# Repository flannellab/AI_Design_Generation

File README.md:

# AI_Design_Generation
Collection of things for AI generation of PCB designs (Components, Schematics, PCBs, Docs)

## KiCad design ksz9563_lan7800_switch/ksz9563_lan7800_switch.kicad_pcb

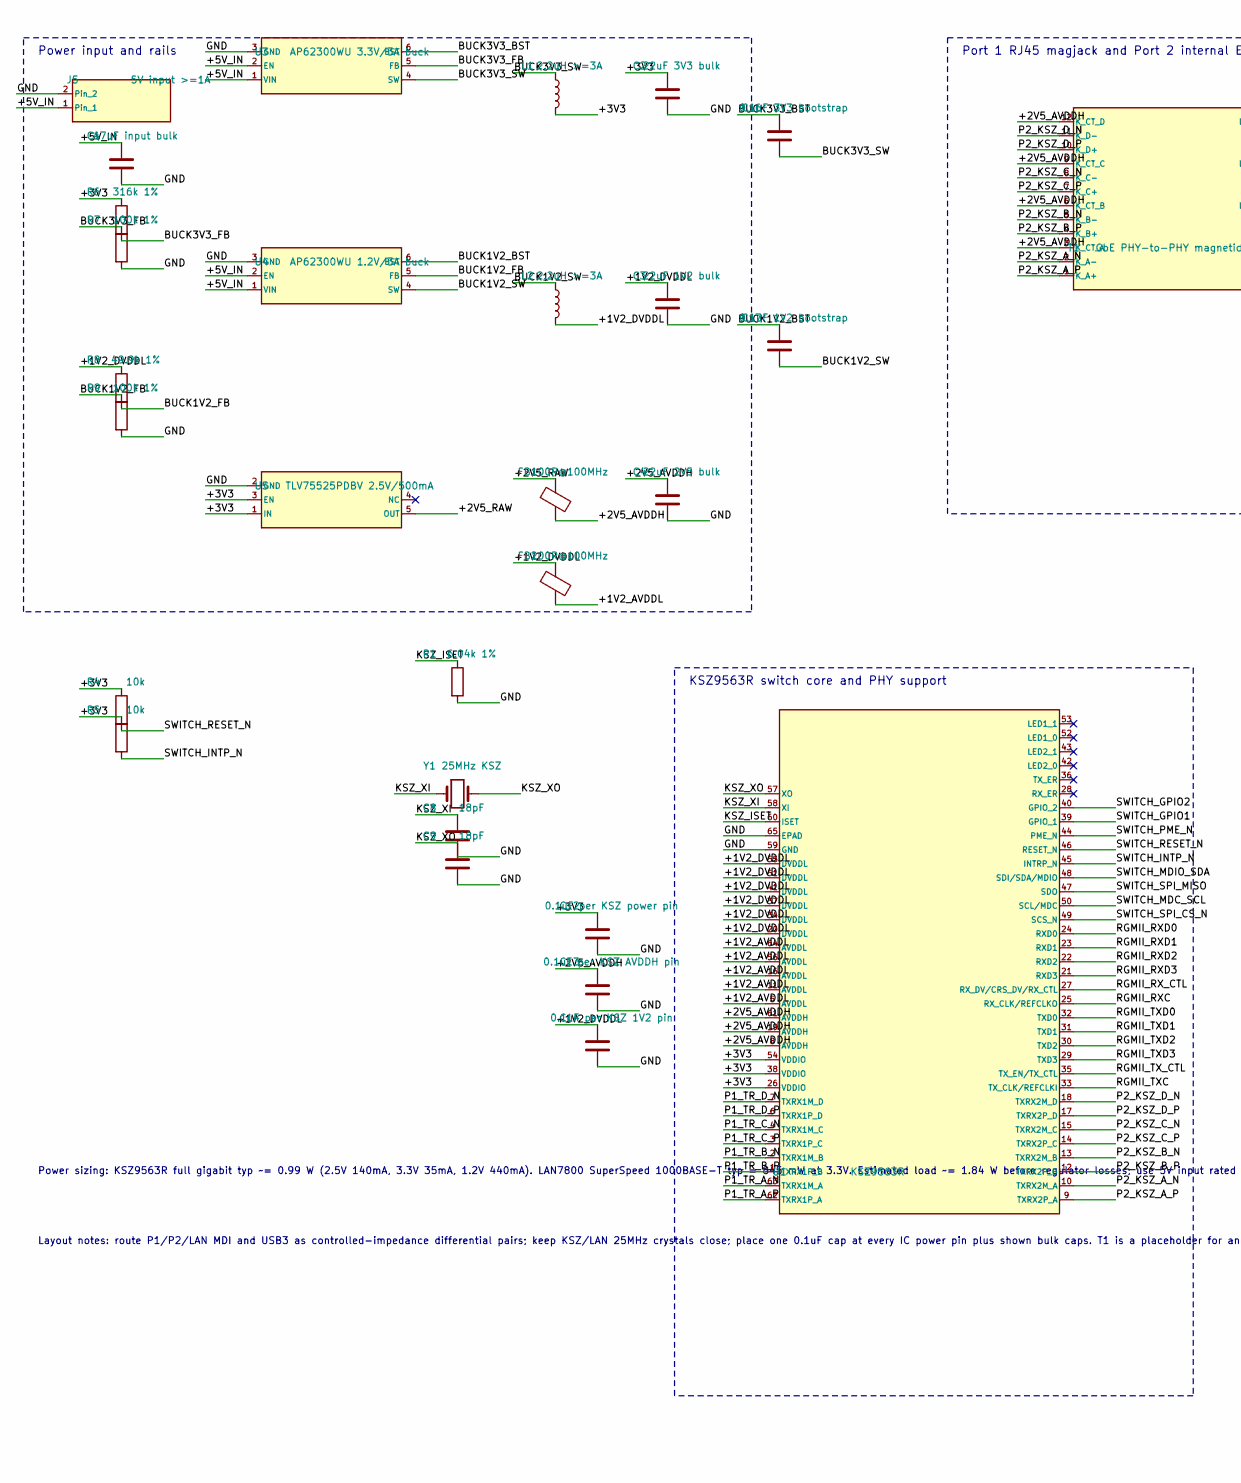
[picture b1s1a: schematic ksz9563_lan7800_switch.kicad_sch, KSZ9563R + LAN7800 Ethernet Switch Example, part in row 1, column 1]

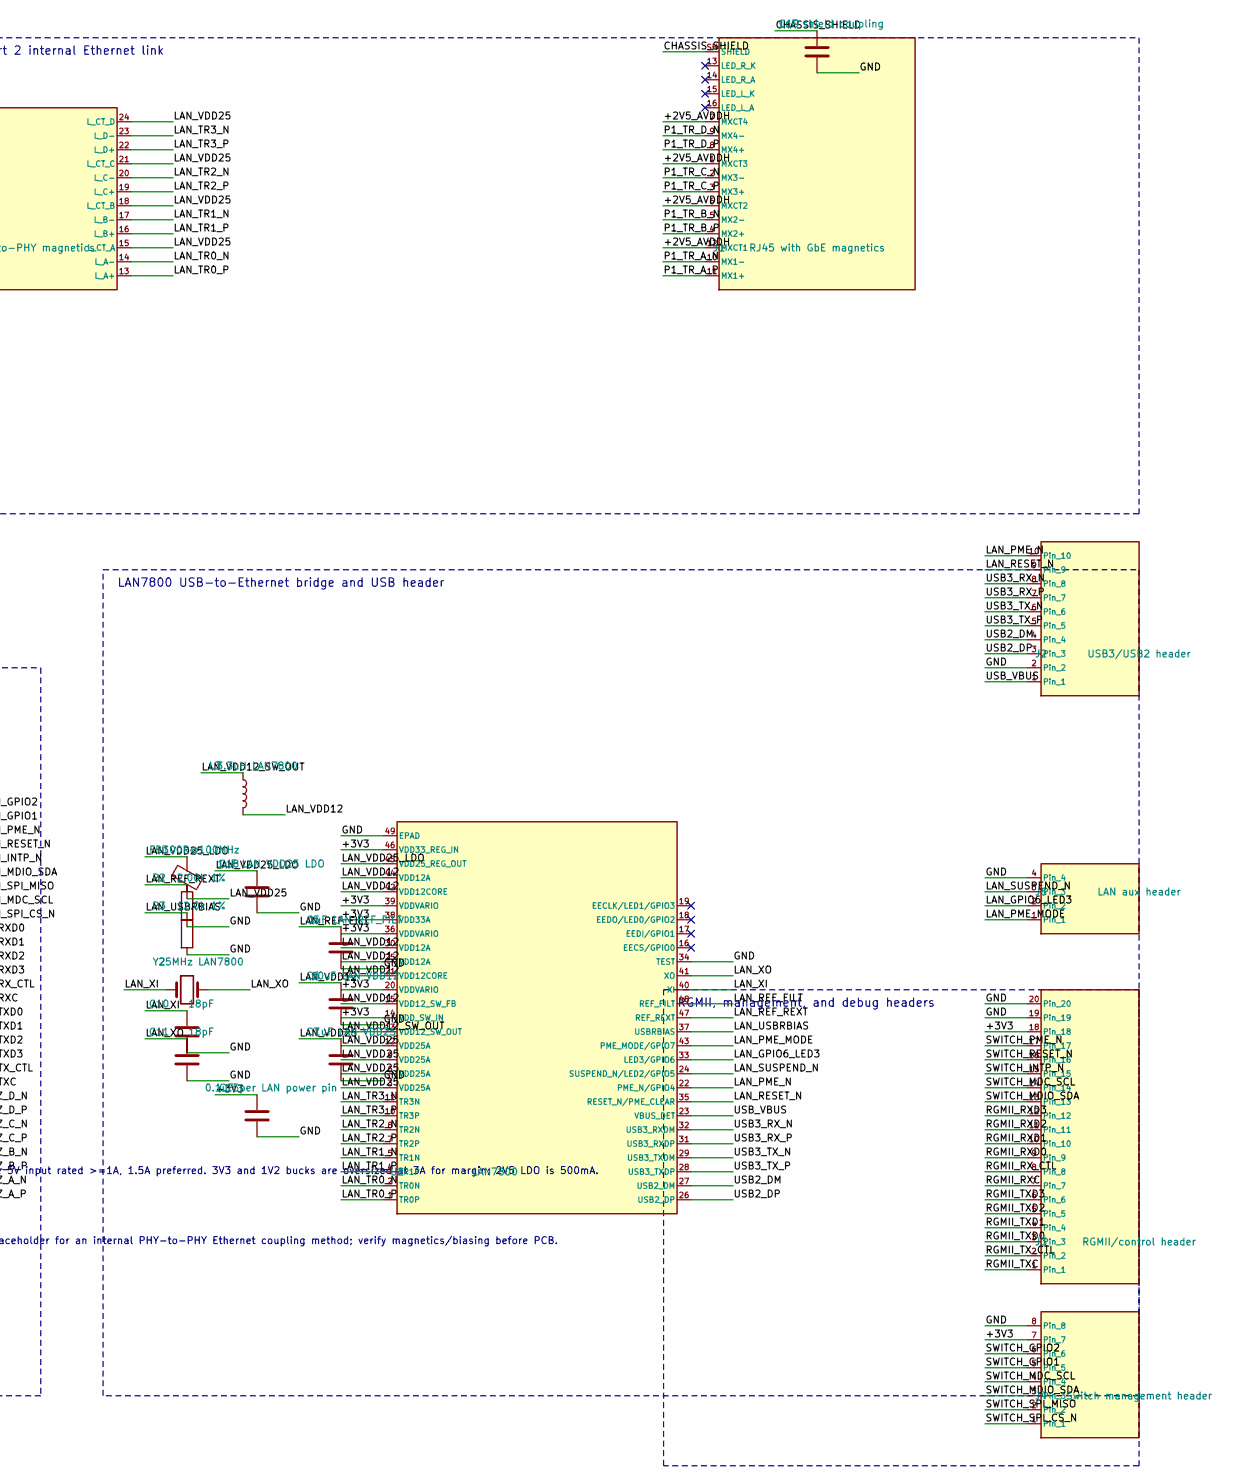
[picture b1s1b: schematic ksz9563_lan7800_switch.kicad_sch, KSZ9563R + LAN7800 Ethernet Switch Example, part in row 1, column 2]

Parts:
C1: 47uF input bulk; C_1206_3216Metric; MPN GRM31CR61A476ME15L
C2: 22uF 3V3 bulk; C_0603_1608Metric; MPN GRM188R60J226MEA0D
C3: 22uF 1V2 bulk; C_0603_1608Metric; MPN GRM188R60J226MEA0D
C4: 22uF 2V5 bulk; C_0603_1608Metric; MPN GRM188R60J226MEA0D
C5: 1uF LAN REF_FILT; C_0402_1005Metric; MPN GRM155R61A105KE15D
C6: 10uF LAN VDD12; C_0402_1005Metric; MPN GRM155R60J106ME15D
C7: 1uF LAN VDD25; C_0402_1005Metric; MPN GRM155R61A105KE15D
C8, C9, C10, C11: 18pF; C_0402_1005Metric; MPN GRM1555C1H180JA01D
C12: 0.1uF per KSZ power pin; C_0402_1005Metric; MPN GRM155R71C104KA88D
C13: 0.1uF per KSZ AVDDH pin; C_0402_1005Metric; MPN GRM155R71C104KA88D
C14: 0.1uF per KSZ 1V2 pin; C_0402_1005Metric; MPN GRM155R71C104KA88D
C15: 0.1uF per LAN power pin; C_0402_1005Metric; MPN GRM155R71C104KA88D
C16: 0.1uF 3V3 bootstrap; C_0402_1005Metric; MPN GRM155R71C104KA88D
C17: 0.1uF 1V2 bootstrap; C_0402_1005Metric; MPN GRM155R71C104KA88D
C18: 1uF LAN VDD25 LDO; C_0402_1005Metric; MPN GRM155R61A105KE15D
C19: 1nF shield coupling; C_0402_1005Metric; MPN GRM1555C1H102JA01D
FB1, FB2, FB3: 100R@100MHz; L_0402_1005Metric; MPN BLM15AG121SN1D
J1: RJ45 with GbE magnetics; RJ45_Pulse_JK0654219NL_Horizontal; MPN JK0654219NL
J2: USB3/USB2 header; PinHeader_1x10_P2.54mm_Vertical; MPN TSW-110-07-G-S
J3: RGMII/control header; PinHeader_1x20_P2.54mm_Vertical; MPN TSW-120-07-G-S
J4: Switch management header; PinHeader_1x08_P2.54mm_Vertical; MPN TSW-108-07-G-S
J5: 5V input >=1A; PinHeader_1x02_P2.54mm_Vertical; MPN TSW-102-07-G-S
J6: LAN aux header; PinHeader_1x04_P2.54mm_Vertical; MPN TSW-104-07-G-S
L1, L2: 2.2uH >=3A; L_Bourns_SRN6045TA; MPN SRN6045TA-2R2Y
L3: 3.3uH LAN7800; L_Bourns-SRN4018; MPN SRN4018-3R3M
R1: 6.04k 1%; R_0402_1005Metric; MPN CRCW04026K04FKED
R2: 2.00k 1%; R_0402_1005Metric; MPN CRCW04022K00FKED
R3: 12.0k 1%; R_0402_1005Metric; MPN CRCW040212K0FKED
R4, R5: 10k; R_0402_1005Metric; MPN CRCW040210K0FKED
R6: 316k 1%; R_0402_1005Metric; MPN CRCW0402316KFKED
R7, R9: 100k 1%; R_0402_1005Metric; MPN CRCW0402100KFKED
R8: 49.9k 1%; R_0402_1005Metric; MPN CRCW040249K9FKED
T1: GbE PHY-to-PHY magnetics; Transformer_Ethernet_YDS_30F-51NL_SO-24_7.1x15.1mm; MPN 30F-51NL
U1: KSZ9563R; QFN-64-1EP_8x8mm_P0.4mm_EP6.5x6.5mm_ThermalVias; MPN KSZ9563RNXI
U2: LAN7800; QFN-48-1EP_6x6mm_P0.4mm_EP4.3x4.3mm_ThermalVias; MPN LAN7800-I/Y9X
U3: AP62300WU 3.3V/3A buck; TSOT-23-6; MPN AP62300WU-7
U4: AP62300WU 1.2V/3A buck; TSOT-23-6; MPN AP62300WU-7
U5: TLV75525PDBV 2.5V/500mA; SOT-23-5; MPN TLV75525PDBVR
Y1: 25MHz KSZ; Crystal_SMD_3225-4Pin_3.2x2.5mm; MPN ABM8G-25.000MHZ-B4Y-T
Y2: 25MHz LAN7800; Crystal_SMD_3225-4Pin_3.2x2.5mm; MPN ABM8G-25.000MHZ-B4Y-T

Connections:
/+1V2_AVDDL: FB2.2, U1.5 (AVDDL), U1.11 (AVDDL), U1.16 (AVDDL), U1.56 (AVDDL), U1.64 (AVDDL)
/+1V2_DVDDL: C3.1, C14.1, FB2.1, L2.2, R8.1, U1.20 (DVDDL), U1.34 (DVDDL), U1.37 (DVDDL), U1.41 (DVDDL), U1.51 (DVDDL), U1.55 (DVDDL)
/+2V5_AVDDH: C4.1, C13.1, FB1.2, J1.1 (MXCT3), J1.6 (MXCT2), J1.7 (MXCT4), J1.12 (MXCT1), T1.3 (K_CT_A), T1.6 (K_CT_B), T1.9 (K_CT_C), T1.12 (K_CT_D), U1.8 (AVDDH), U1.19 (AVDDH), U1.61 (AVDDH)
/+2V5_RAW: FB1.1, U5.5 (OUT)
/+3V3: C2.1, C12.1, C15.1, J3.18, J4.7, L1.2, R4.1, R5.1, R6.1, U1.26 (VDDIO), U1.38 (VDDIO), U1.54 (VDDIO), U2.14 (VDD_SW_IN), U2.20 (VDDVARIO), U2.36 (VDDVARIO), U2.38 (VDD33A), U2.39 (VDDVARIO), U2.46 (VDD33_REG_IN), U5.1 (IN), U5.3 (EN)
/+5V_IN: C1.1, J5.1, U3.1 (VIN), U3.2 (EN), U4.1 (VIN), U4.2 (EN)
/BUCK1V2_BST: C17.1, U4.6 (BST)
/BUCK1V2_FB: R8.2, R9.1, U4.5 (FB)
/BUCK1V2_SW: C17.2, L2.1, U4.4 (SW)
/BUCK3V3_BST: C16.1, U3.6 (BST)
/BUCK3V3_FB: R6.2, R7.1, U3.5 (FB)
/BUCK3V3_SW: C16.2, L1.1, U3.4 (SW)
/CHASSIS_SHIELD: C19.1, J1.SH (SHIELD)
/GND: C1.2, C2.2, C3.2, C4.2, C5.2, C6.2, C7.2, C8.2, C9.2, C10.2, C11.2, C12.2, C13.2, C14.2, C15.2, C18.2, C19.2, J2.2, J3.19, J3.20, J4.8, J5.2, J6.4, R1.2, R2.2, R3.2, R7.2, R9.2, U1.59 (GND), U1.65 (EPAD), U2.34 (TEST), U2.49 (EPAD), U3.3 (GND), U4.3 (GND), U5.2 (GND)
/KSZ_ISET: R1.1, U1.60 (ISET)
/KSZ_XI: C8.1, U1.58 (XI), Y1.1
/KSZ_XO: C9.1, U1.57 (XO), Y1.2
/LAN_GPIO6_LED3: J6.2, U2.33 (LED3/GPIO6)
/LAN_PME_MODE: J6.1, U2.43 (PME_MODE/GPIO7)
/LAN_PME_N: J2.10, U2.22 (PME_N/GPIO4)
/LAN_REF_FILT: C5.1, U2.48 (REF_FILT)
/LAN_REF_REXT: R2.1, U2.47 (REF_REXT)
/LAN_RESET_N: J2.9, U2.35 (RESET_N/PME_CLEAR)
/LAN_SUSPEND_N: J6.3, U2.24 (SUSPEND_N/LED2/GPIO5)
/LAN_TR0_N: T1.14 (L_A-), U2.2 (TR0N)
/LAN_TR0_P: T1.13 (L_A+), U2.1 (TR0P)
/LAN_TR1_N: T1.17 (L_B-), U2.5 (TR1N)
/LAN_TR1_P: T1.16 (L_B+), U2.4 (TR1P)
/LAN_TR2_N: T1.20 (L_C-), U2.8 (TR2N)
/LAN_TR2_P: T1.19 (L_C+), U2.7 (TR2P)
/LAN_TR3_N: T1.23 (L_D-), U2.11 (TR3N)
/LAN_TR3_P: T1.22 (L_D+), U2.10 (TR3P)
/LAN_USBRBIAS: R3.1, U2.37 (USBRBIAS)
/LAN_VDD12: C6.1, L3.2, U2.15 (VDD12_SW_FB), U2.21 (VDD12CORE), U2.25 (VDD12A), U2.30 (VDD12A), U2.42 (VDD12CORE), U2.44 (VDD12A)
/LAN_VDD12_SW_OUT: L3.1, U2.13 (VDD12_SW_OUT)
/LAN_VDD25: C7.1, FB3.2, T1.15 (L_CT_A), T1.18 (L_CT_B), T1.21 (L_CT_C), T1.24 (L_CT_D), U2.3 (VDD25A), U2.6 (VDD25A), U2.9 (VDD25A), U2.12 (VDD25A)
/LAN_VDD25_LDO: C18.1, FB3.1, U2.45 (VDD25_REG_OUT)
/LAN_XI: C10.1, U2.40 (XI), Y2.1
/LAN_XO: C11.1, U2.41 (XO), Y2.2
/P1_TR_A_N: J1.10 (MX1-), U1.63 (TXRX1M_A)
/P1_TR_A_P: J1.11 (MX1+), U1.62 (TXRX1P_A)
/P1_TR_B_N: J1.5 (MX2-), U1.2 (TXRX1M_B)
/P1_TR_B_P: J1.4 (MX2+), U1.1 (TXRX1P_B)
/P1_TR_C_N: J1.2 (MX3-), U1.4 (TXRX1M_C)
/P1_TR_C_P: J1.3 (MX3+), U1.3 (TXRX1P_C)
/P1_TR_D_N: J1.9 (MX4-), U1.7 (TXRX1M_D)
/P1_TR_D_P: J1.8 (MX4+), U1.6 (TXRX1P_D)
/P2_KSZ_A_N: T1.2 (K_A-), U1.10 (TXRX2M_A)
/P2_KSZ_A_P: T1.1 (K_A+), U1.9 (TXRX2P_A)
/P2_KSZ_B_N: T1.5 (K_B-), U1.13 (TXRX2M_B)
/P2_KSZ_B_P: T1.4 (K_B+), U1.12 (TXRX2P_B)
/P2_KSZ_C_N: T1.8 (K_C-), U1.15 (TXRX2M_C)
/P2_KSZ_C_P: T1.7 (K_C+), U1.14 (TXRX2P_C)
/P2_KSZ_D_N: T1.11 (K_D-), U1.18 (TXRX2M_D)
/P2_KSZ_D_P: T1.10 (K_D+), U1.17 (TXRX2P_D)
/RGMII_RXC: J3.7, U1.25 (RX_CLK/REFCLKO)
/RGMII_RXD0: J3.9, U1.24 (RXD0)
/RGMII_RXD1: J3.10, U1.23 (RXD1)
/RGMII_RXD2: J3.11, U1.22 (RXD2)
/RGMII_RXD3: J3.12, U1.21 (RXD3)
/RGMII_RX_CTL: J3.8, U1.27 (RX_DV/CRS_DV/RX_CTL)
/RGMII_TXC: J3.1, U1.33 (TX_CLK/REFCLKI)
/RGMII_TXD0: J3.3, U1.32 (TXD0)
/RGMII_TXD1: J3.4, U1.31 (TXD1)
/RGMII_TXD2: J3.5, U1.30 (TXD2)
/RGMII_TXD3: J3.6, U1.29 (TXD3)
/RGMII_TX_CTL: J3.2, U1.35 (TX_EN/TX_CTL)
/SWITCH_GPIO1: J4.5, U1.39 (GPIO_1)
/SWITCH_GPIO2: J4.6, U1.40 (GPIO_2)
/SWITCH_INTP_N: J3.15, R5.2, U1.45 (INTRP_N)
/SWITCH_MDC_SCL: J3.14, J4.4, U1.50 (SCL/MDC)
/SWITCH_MDIO_SDA: J3.13, J4.3, U1.48 (SDI/SDA/MDIO)
/SWITCH_PME_N: J3.17, U1.44 (PME_N)
/SWITCH_RESET_N: J3.16, R4.2, U1.46 (RESET_N)
/SWITCH_SPI_CS_N: J4.1, U1.49 (SCS_N)
/SWITCH_SPI_MISO: J4.2, U1.47 (SDO)
/USB2_DM: J2.4, U2.27 (USB2_DM)
/USB2_DP: J2.3, U2.26 (USB2_DP)
/USB3_RX_N: J2.8, U2.32 (USB3_RXDM)
/USB3_RX_P: J2.7, U2.31 (USB3_RXDP)
/USB3_TX_N: J2.6, U2.29 (USB3_TXDM)
/USB3_TX_P: J2.5, U2.28 (USB3_TXDP)
/USB_VBUS: J2.1, U2.23 (VBUS_DET)

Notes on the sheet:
Power input and rails
KSZ9563R switch core and PHY support
Port 1 RJ45 magjack and Port 2 internal Ethernet link
LAN7800 USB-to-Ethernet bridge and USB header
RGMII, management, and debug headers
Power sizing: KSZ9563R full gigabit typ ~= 0.99 W (2.5V 140mA, 3.3V 35mA, 1.2V 440mA). LAN7800 SuperSpeed 1000BASE-T typ = 845 mW at 3.3V. Estimated load ~= 1.84 W before regulator losses; use 5V input rated >=1A, 1.5A preferred. 3V3 and 1V2 bucks are oversized at 3A for margin; 2V5 LDO is 500mA.
Layout notes: route P1/P2/LAN MDI and USB3 as controlled-impedance differential pairs; keep KSZ/LAN 25MHz crystals close; place one 0.1uF cap at every IC power pin plus shown bulk caps. T1 is a placeholder for an internal PHY-to-PHY Ethernet coupling method; verify magnetics/biasing before PCB.

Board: 2 copper layers, 48 parts (0 on the bottom side), 83 nets, no tracks yet.

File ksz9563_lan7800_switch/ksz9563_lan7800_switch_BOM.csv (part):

Item,Qty,References,Value,Footprint,Manufacturer,MPN,Mfr_Region,Notes,Description,Datasheet,Source
1,1,C1,47uF input bulk,Capacitor_SMD:C_1206_3216Metric,Murata Electronics,GRM31CR61A476ME15L,Japan-based,,Capacitor,,https://www.murata.com/en-us/products/productdetail?partno=G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
2,1,C2,22uF 3V3 bulk,Capacitor_SMD:C_0603_1608Metric,Murata Electronics,GRM188R60J226MEA0D,Japan-based,,Capacitor,,https://www.murata.com/en-us/products/productdetail?partno=G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
3,1,C3,22uF 1V2 bulk,Capacitor_SMD:C_0603_1608Metric,Murata Electronics,GRM188R60J226MEA0D,Japan-based,,Capacitor,,https://www.murata.com/en-us/products/productdetail?partno=G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
4,1,C4,22uF 2V5 bulk,Capacitor_SMD:C_0603_1608Metric,Murata Electronics,GRM188R60J226MEA0D,Japan-based,,Capacitor,,https://www.murata.com/en-us/products/productdetail?partno=G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
5,1,C5,1uF LAN REF_FILT,Capacitor_SMD:C_0402_1005Metric,Murata Electronics,GRM155R61A105KE15D,Japan-based,,Capacitor,,https://www.digikey.com/en/products/detail/murata-electronic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
6,1,C6,10uF LAN VDD12,Capacitor_SMD:C_0402_1005Metric,Murata Electronics,GRM155R60J106ME15D,Japan-based,,Capacitor,,https://www.murata.com/en-us/products/productdetail?partno=G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
7,1,C7,1uF LAN VDD25,Capacitor_SMD:C_0402_1005Metric,Murata Electronics,GRM155R61A105KE15D,Japan-based,,Capacitor,,https://www.digikey.com/en/products/detail/murata-electronic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
8,4,"C8, C9, C10, C11",18pF,Capacitor_SMD:C_0402_1005Metric,Murata Electronics,GRM1555C1H180JA01D,Japan-based,,Capacitor,,https://www.digikey.com/en/products/detail/murata-electronic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
9,1,C12,0.1uF per KSZ power pin,Capacitor_SMD:C_0402_1005Metric,Murata Electronics,GRM155R71C104KA88D,Japan-based,,Capacitor,,https://www.murata.com/en-us/products/productdetail?partno=G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
10,1,C13,0.1uF per KSZ AVDDH pin,Capacitor_SMD:C_0402_1005Metric,Murata Electronics,GRM155R71C104KA88D,Japan-based,,Capacitor,,https://www.murata.com/en-us/products/productdetail?partno=G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
11,1,C14,0.1uF per KSZ 1V2 pin,Capacitor_SMD:C_0402_1005Metric,Murata Electronics,GRM155R71C104KA88D,Japan-based,,Capacitor,,https://www.murata.com/en-us/products/productdetail?partno=G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
12,1,C15,0.1uF per LAN power pin,Capacitor_SMD:C_0402_1005Metric,Murata Electronics,GRM155R71C104KA88D,Japan-based,,Capacitor,,https://www.murata.com/en-us/products/productdetail?partno=G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
13,1,C16,0.1uF 3V3 bootstrap,Capacitor_SMD:C_0402_1005Metric,Murata Electronics,GRM155R71C104KA88D,Japan-based,,Capacitor,,https://www.murata.com/en-us/products/productdetail?partno=G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
14,1,C17,0.1uF 1V2 bootstrap,Capacitor_SMD:C_0402_1005Metric,Murata Electronics,GRM155R71C104KA88D,Japan-based,,Capacitor,,https://www.murata.com/en-us/products/productdetail?partno=G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
15,1,C18,1uF LAN VDD25 LDO,Capacitor_SMD:C_0402_1005Metric,Murata Electronics,GRM155R61A105KE15D,Japan-based,,Capacitor,,https://www.digikey.com/en/products/detail/murata-electronic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
16,1,C19,1nF shield coupling,Capacitor_SMD:C_0402_1005Metric,Murata Electronics,GRM1555C1H102JA01D,Japan-based,,Capacitor,,https://www.digikey.com/en/products/detail/murata-electronic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
17,3,"FB1, FB2, FB3",100R@100MHz,Inductor_SMD:L_0402_1005Metric,Murata Electronics,BLM15AG121SN1D,Japan-based,,Ferrite bead,,https://www.digikey.com/en/products/detail/murata-electronic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
18,1,J1,RJ45 with GbE magnetics,Connector_RJ:RJ45_Pulse_JK0654219NL_Horizontal,Pulse Electronics,JK0654219NL,USA-based legacy Pulse; verify current supply chain,10/100/1000Base-T MagJack; LEDs intentionally left NC in this first-pass schematic,1-port 10/100/1000Base-T RJ45 MagJack with integrated magnetics and LEDs,https://datasheet4u.com/pdf-down/J/K/0/JK0654219_PulseATechn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,https://datasheet4u.com/pdf-down/J/K/0/JK0654219_PulseATechn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
19,1,J2,USB3/USB2 header,Connector_PinHeader_2.54mm:PinHeader_1x10_P2.54mm_Vertical,Samtec,TSW-110-07-G-S,USA-based,,1x10 2.54mm male header,,https://www.samtec.com/products/tsw-110-07-g-s-010
20,1,J3,RGMII/control header,Connector_PinHeader_2.54mm:PinHeader_1x20_P2.54mm_Vertical,Samtec,TSW-120-07-G-S,USA-based,,1x20 2.54mm male header,,https://www.samtec.com/products/tsw-120-07-g-s
21,1,J4,Switch management header,Connector_PinHeader_2.54mm:PinHeader_1x08_P2.54mm_Vertical,Samtec,TSW-108-07-G-S,USA-based,,1x8 2.54mm male header,,https://www.samtec.com/products/tsw-108-07-g-s
22,1,J5,5V input >=1A,Connector_PinHeader_2.54mm:PinHeader_1x02_P2.54mm_Vertical,Samtec,TSW-102-07-G-S,USA-based,,1x2 2.54mm male header,,https://www.samtec.com/products/tsw-102-07-g-s
23,1,J6,LAN aux header,Connector_PinHeader_2.54mm:PinHeader_1x04_P2.54mm_Vertical,Samtec,TSW-104-07-G-S,USA-based,,1x4 2.54mm male header,,https://www.samtec.com/products/tsw-104-07-g-s
24,2,"L1, L2",2.2uH >=3A,Inductor_SMD:L_Bourns_SRN6045TA,Bourns,SRN6045TA-2R2Y,USA-based,,Inductor,,https://www.bourns.com/products/magnetic-products/details/po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
25,1,L3,3.3uH LAN7800,Inductor_SMD:L_Bourns-SRN4018,Bourns,SRN4018-3R3M,USA-based,,Inductor,,https://www.bourns.com/docs/product-datasheets/srn4018.pdf
26,1,R1,6.04k 1%,Resistor_SMD:R_0402_1005Metric,Vishay Dale,CRCW04026K04FKED,USA-based,,Resistor,,https://www.vishay.com/en/resistors-linear/fixed/surface-mou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
27,1,R2,2.00k 1%,Resistor_SMD:R_0402_1005Metric,Vishay Dale,CRCW04022K00FKED,USA-based,,Resistor,,https://www.vishay.com/en/resistors-linear/fixed/surface-mou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
28,1,R3,12.0k 1%,Resistor_SMD:R_0402_1005Metric,Vishay Dale,CRCW040212K0FKED,USA-based,,Resistor,,https://www.vishay.com/en/resistors-linear/fixed/surface-mou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
29,2,"R4, R5",10k,Resistor_SMD:R_0402_1005Metric,Vishay Dale,CRCW040210K0FKED,USA-based,,Resistor,,https://www.vishay.com/en/resistors-linear/fixed/surface-mou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
30,1,R6,316k 1%,Resistor_SMD:R_0402_1005Metric,Vishay Dale,CRCW0402316KFKED,USA-based,,Resistor,,https://www.vishay.com/en/resistors-linear/fixed/surface-mou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
31,2,"R7, R9",100k 1%,Resistor_SMD:R_0402_1005Metric,Vishay Dale,CRCW0402100KFKED,USA-based,,Resistor,,https://www.vishay.com/en/resistors-linear/fixed/surface-mou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
32,1,R8,49.9k 1%,Resistor_SMD:R_0402_1005Metric,Vishay Dale,CRCW040249K9FKED,USA-based,,Resistor,,https://www.vishay.com/en/resistors-linear/fixed/surface-mou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
33,1,T1,GbE PHY-to-PHY magnetics,Transformer_SMD:Transformer_Ethernet_YDS_30F-51NL_SO-24_7.1x15.1mm,YDS Tech,30F-51NL,China-based exception,Matches KiCad library footprint; replace with a non-China qualified magnetics part before release if required,Placeholder 1000BASE-T isolation/coupling transformer for internal PHY-to-PHY link,,https://www.lcsc.com/product-detail/C123168.html
34,1,U1,KSZ9563R,Package_DFN_QFN:QFN-64-1EP_8x8mm_P0.4mm_EP6.5x6.5mm_ThermalVias,Microchip Technology,KSZ9563RNXI,USA-based,,"Microchip 3-port gigabit Ethernet switch, 2 PHY + RGMII/MII/RMII MAC port",https://ww1.microchip.com/downloads/aemDocuments/documents/O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,https://www.microchip.com/en-us/product/ksz9563
35,1,U2,LAN7800,Package_DFN_QFN:QFN-48-1EP_6x6mm_P0.4mm_EP4.3x4.3mm_ThermalVias,Microchip Technology,LAN7800-I/Y9X,USA-based,,Microchip SuperSpeed USB 3.1 Gen 1 to 10/100/1000 Ethernet controller,https://ww1.microchip.com/downloads/aemDocuments/documents/U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,https://www.microchip.com/en-us/product/lan7800
36,1,U3,AP62300WU 3.3V/3A buck,Package_TO_SOT_SMD:TSOT-23-6,Diodes Incorporated,AP62300WU-7,USA-based,,3A adjustable buck regulator,,https://www.diodes.com/part/view/AP62300
37,1,U4,AP62300WU 1.2V/3A buck,Package_TO_SOT_SMD:TSOT-23-6,Diodes Incorporated,AP62300WU-7,USA-based,,3A adjustable buck regulator,,https://www.diodes.com/part/view/AP62300
38,1,U5,TLV75525PDBV 2.5V/500mA,Package_TO_SOT_SMD:SOT-23-5,Texas Instruments,TLV75525PDBVR,USA-based,,"TI 500mA low-Iq LDO, fixed 2.5V output",https://www.ti.com/lit/ds/symlink/tlv755p.pdf,https://www.ti.com/product/TLV755P
39,1,Y1,25MHz KSZ,Crystal:Crystal_SMD_3225-4Pin_3.2x2.5mm,Abracon,ABM8G-25.000MHZ-B4Y-T,USA-based,Load caps should be tuned against the selected crystal CL and board parasitics,25MHz crystal,,https://www.digikey.com/en/products/detail/abracon-llc/ABM8G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

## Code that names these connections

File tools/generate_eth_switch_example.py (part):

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        ("45", "INTRP_N", "SWITCH_INTP_N"),
        ("46", "RESET_N", "SWITCH_RESET_N"),
        ("44", "PME_N", "SWITCH_PME_N"),
        ("39", "GPIO_1", "SWITCH_GPIO1"),
        ("40", "GPIO_2", "SWITCH_GPIO2"),
    ]:
        add(Pin(num, name, "R", net=net))
    for num, name in [("28", "RX_ER"), ("36", "TX_ER"), ("42", "LED2_0"), ("43", "LED2_1"), ("52", "LED1_0"), ("53", "LED1_1")]:
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        ("32", "USB3_RXDM", "USB3_RX_N"),
        ("23", "VBUS_DET", "USB_VBUS"),
        ("35", "RESET_N/PME_CLEAR", "LAN_RESET_N"),
        ("22", "PME_N/GPIO4", "LAN_PME_N"),
        ("24", "SUSPEND_N/LED2/GPIO5", "LAN_SUSPEND_N"),
        ("33", "LED3/GPIO6", "LAN_GPIO6_LED3"),
        ("43", "PME_MODE/GPIO7", "LAN_PME_MODE"),
        ("37", "USBRBIAS", "LAN_USBRBIAS"),
        ("47", "REF_REXT", "LAN_REF_REXT"),
        ("48", "REF_FILT", "LAN_REF_FILT"),
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        }),
        add_manual_component(syms["hdr8"], "J4", "Switch management header", 420.37, 269.24, {
            "1": "SWITCH_SPI_CS_N", "2": "SWITCH_SPI_MISO", "3": "SWITCH_MDIO_SDA", "4": "SWITCH_MDC_SCL",
            "5": "SWITCH_GPIO1", "6": "SWITCH_GPIO2", "7": "+3V3", "8": "GND",
        }),
        add_manual_component(syms["hdr4"], "J6", "LAN aux header", 420.37, 177.8, {
            "1": "LAN_PME_MODE", "2": "LAN_GPIO6_LED3", "3": "LAN_SUSPEND_N", "4": "GND",
        }),
        add_manual_component(syms["hdr2"], "J5", "5V input >=1A", 35.56, 30.48, {"1": "+5V_IN", "2": "GND"}),
        add_manual_component(syms["buck"], "U3", "AP62300WU 3.3V/3A buck", 73.66, 25.4, {
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        add_lib_component("Device:L", "L1", "2.2uH >=3A", "Inductor_SMD:L_Bourns_SRN6045TA", 114.3, 27.94, {"1": "BUCK3V3_SW", "2": "+3V3"}, desc="Inductor"),
        add_lib_component("Device:L", "L2", "2.2uH >=3A", "Inductor_SMD:L_Bourns_SRN6045TA", 114.3, 66.04, {"1": "BUCK1V2_SW", "2": "+1V2_DVDDL"}, desc="Inductor"),
        add_lib_component("Device:L", "L3", "3.3uH LAN7800", "Inductor_SMD:L_Bourns-SRN4018", 266.7, 154.94, {"1": "LAN_VDD12_SW_OUT", "2": "LAN_VDD12"}, desc="Inductor"),
        add_lib_component("Device:Crystal", "Y1", "25MHz KSZ", "Crystal:Crystal_SMD_3225-4Pin_3.2x2.5mm", 96.52, 154.94, {"1": "KSZ_XI", "2": "KSZ_XO"}, pin_style="horizontal", desc="25MHz crystal"),
        add_lib_component("Device:Crystal", "Y2", "25MHz LAN7800", "Crystal:Crystal_SMD_3225-4Pin_3.2x2.5mm", 256.54, 190.5, {"1": "LAN_XI", "2": "LAN_XO"}, pin_style="horizontal", desc="25MHz crystal"),
    ]

    # Essential support passives, arranged as clean labeled blocks.
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
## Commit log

2026-04-30 Added first drafts of context files
    Added first draft of context files for starting a new project at the same point every time.
2026-04-30 Added tools folder and example design
    Codex created a tools folder that had these scripts and things. There was also a folder named "node_modules", but it had too many files in it to upload at once. The ksz9563_lan7800_switch folder is j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
